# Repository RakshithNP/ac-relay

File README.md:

View this project on [CADLAB.io](https://cadlab.io/project/24087). 

# AC Relay

It is a relay controlled by an ESP8266 and a push button. It is powered by the main AC.

### Firmwares

#### Test

This firmware allows you to test the hardware if needed. It will change the relay status each 400 millisenconds when the button is pressed and it will send the push button status via serial communication.

#### AdafruitIO

This firmware is based in the Adafruit example for comumnicate with its MQTT broker called AdafruitIO. You can see more in <a href="https://io.adafruit.com">io.adafruit.com</a>

In order to use it you should set:

- Your WiFi setting
- You Adafruit user name
- API Key from Adafruit IO
- The MQTT feed which will be used in Adafruit IO

#### MQTT

This firmware allows you to communicate with a MQTT broker. For example, you can install your own MQTT broker in a Raspberry Pi.

This is the actual firmware that I am using at home with this circuit, and it is prepared for being working 24/7. It does:

- Recovery after a power failure.
- Wake up message
- Reconnect message
- Serial debug
- WiFi reconnect if the signal is lost
- MQTT Broker reconnect if the signal is lost

### For future revisions

- `LED`: LED as IO instead of Power LED
- `ESP8266`: ESP8266 as SoC instead of the ESP8266-12E module
- `UPS`: Uninterrupted Power System. Cesar Fernández idea
- `Capacitive button`: A capacitive external button that acts as the push button

***

<br /><span xmlns:dct="http://purl.org/dc/terms/" property="dct:title">Home AC relay</span> by <span xmlns:cc="http://creativecommons.org/ns#" property="cc:attributionName">Enrique Gómez</span> licensed by <a rel="license" href="http://creativecommons.org/licenses/by-sa/4.0/">Creative Commons Attribution-ShareAlike 4.0 International License</a>.<br /><br />

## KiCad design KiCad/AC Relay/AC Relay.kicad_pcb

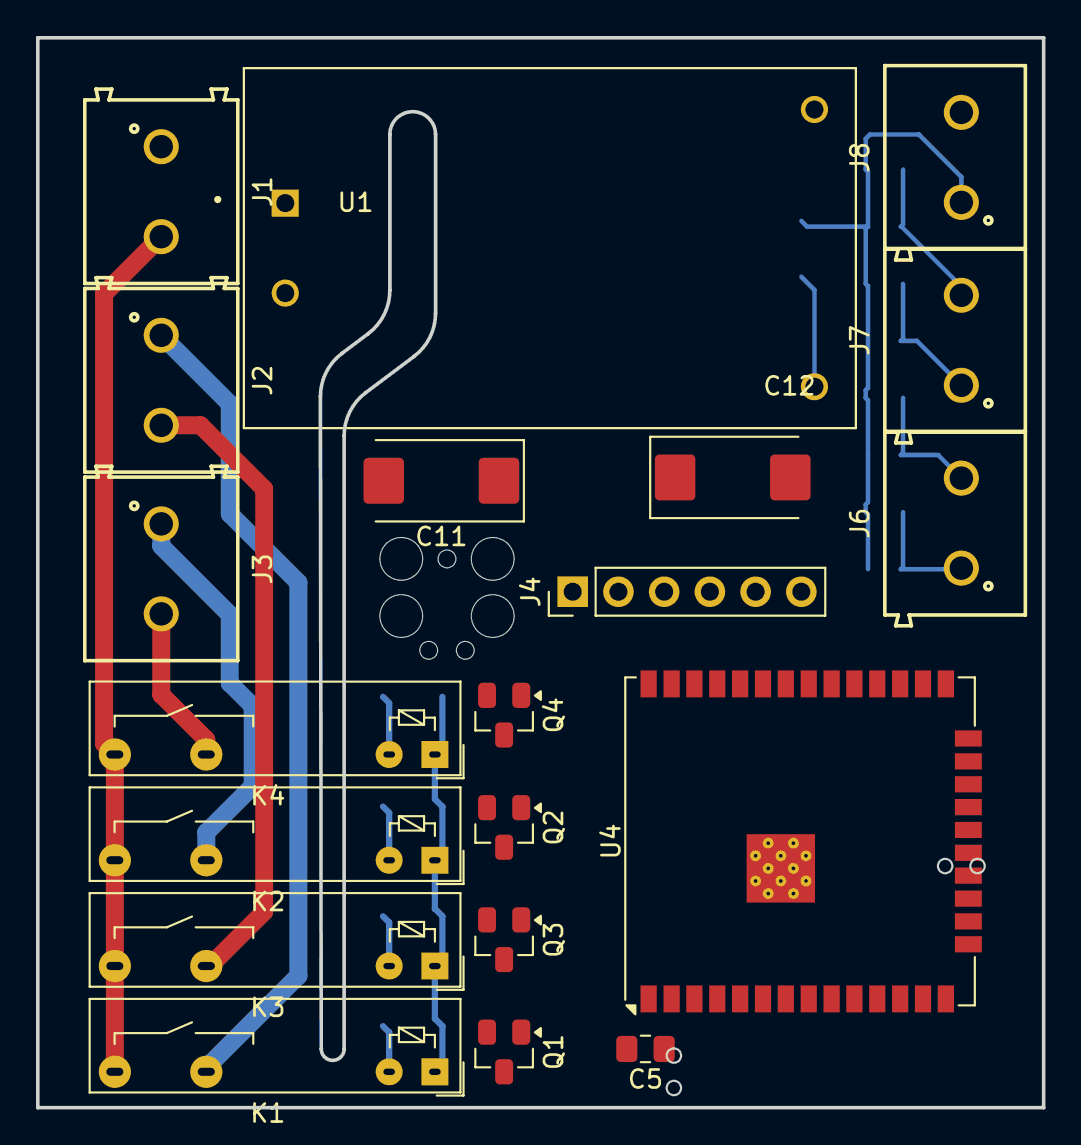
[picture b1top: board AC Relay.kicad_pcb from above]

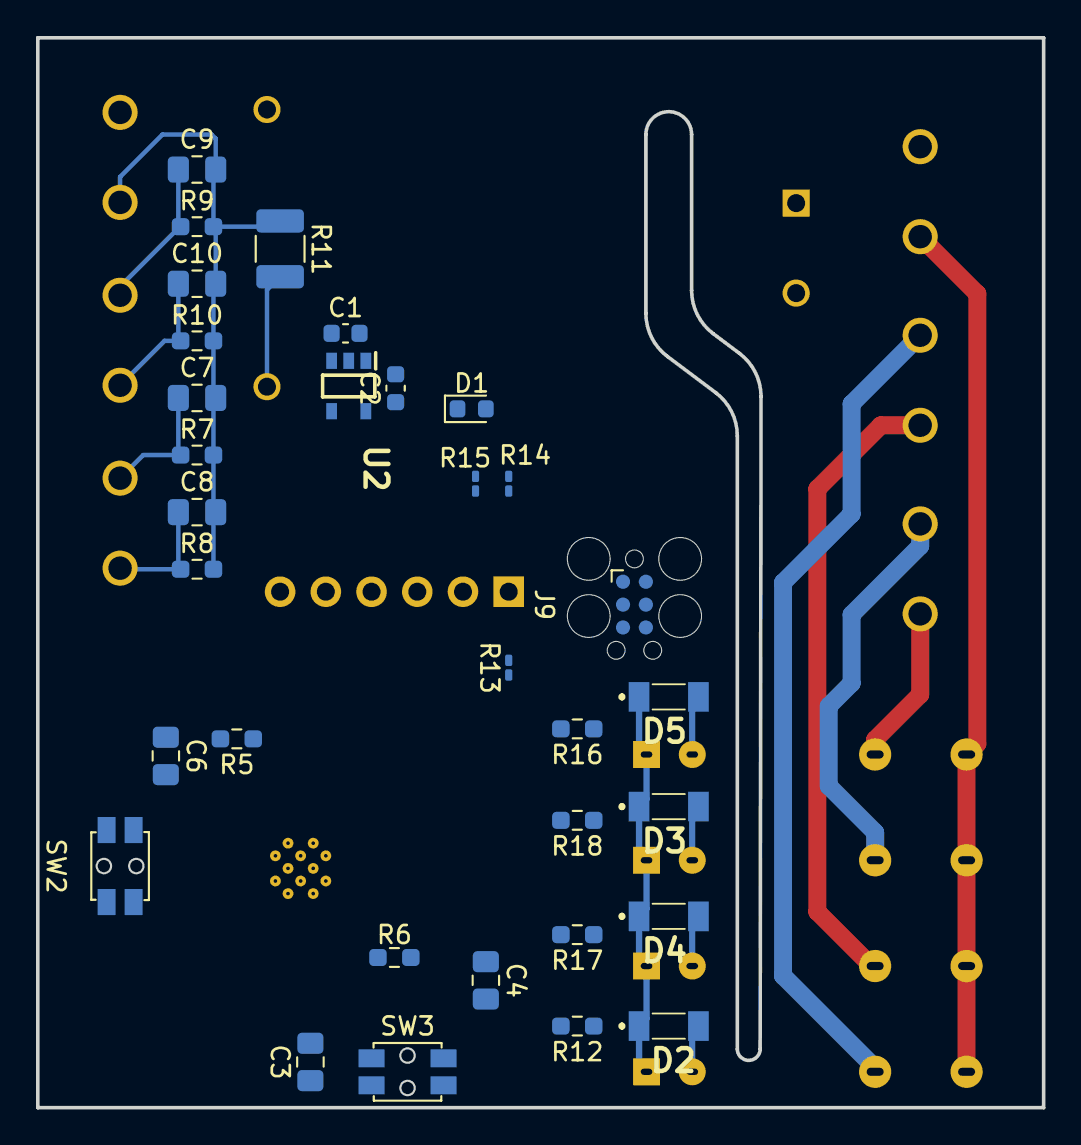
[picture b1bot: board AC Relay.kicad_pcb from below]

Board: 4 copper layers, 55.9 x 59.4 mm, 52 parts (32 on the bottom side), 32 nets.

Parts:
C1, C2: 1uF; C_0603_1608Metric
C3, C5, C6, C7, C8, C9, C10: 0.1uf; C_0805_2012Metric_Pad1.18x1.45mm_HandSolder
C4: 10uf; C_0805_2012Metric_Pad1.18x1.45mm_HandSolder
C11, C12: 100uF T cap; CP_EIA-7343-20_Kemet-V_Pad2.25x2.55mm_HandSolder
D1: LED_verde; LED_0603_1608Metric
D2, D3, D4, D5: LL4148
J1, J2, J3: Screw_Terminal_01x02; 2_terminal_block
J4: Conn_01x06_Female; PinHeader_1x06_P2.54mm_Vertical
J6, J7, J8: TB002-500-02BE; 2_terminal_block_small
J9: Conn_ARM_SWD_TagConnect_TC2030; Tag-Connect_TC2030-IDC-FP_2x03_P1.27mm_Vertical
K1, K2, K3, K4: 1-2071556-1; Relay_SPST_Fanahar_5A
Q1, Q2, Q3, Q4: FDN537N; SuperSOT-3
R5, R7, R8, R9, R10: 10K; R_0603_1608Metric_Pad0.98x0.95mm_HandSolder
R6: 12K; R_0603_1608Metric_Pad0.98x0.95mm_HandSolder
R11: 330R; R_1210_3225Metric_Pad1.30x2.65mm_HandSolder
R12, R16, R17, R18: 1K; R_0603_1608Metric_Pad0.98x0.95mm_HandSolder
R13, R14: 0R; R_0201_0603Metric_Pad0.64x0.40mm_HandSolder
R15: NA; R_0201_0603Metric_Pad0.64x0.40mm_HandSolder
SW2: Boot; SW_SPST_withpost
SW3: Rst; SW_SPST_withpost
U1: HLK-PM01; CONV_HLK-PM01
U2: BU33SD5WG-TR; SOT95P280X125-5N
U4: ESP32-WROOM-32UE

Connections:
+3V3: C2.1, C4.1, C5.1, C12.1, J4.6, R5.1, R6.1, R15.1, U2.5 (VOUT), U4.2 (VDD)
+5V: C1.1, C11.1, D2.1 (K), D3.1 (K), D4.1 (K), D5.1 (K), K1.K1, K2.K1, K3.K1, K4.K1, R11.2, R14.1, U1.4 (+VO), U2.1 (VIN), U2.3 (STBY)
/AC to DC conv/Neutral: J1.1, U1.1 (AC1)
/AC to DC conv/Phase: J1.2, K1.NO, K2.NO, K3.NO, K4.NO, U1.2 (AC2)
/Relay and diver/Rel_sig1: Q1.1 (G), R12.2
/Relay and diver/Rel_sig2: Q3.1 (G), R17.2
/Relay and diver/Rel_sig3: Q2.1 (G), R18.2
/Relay and diver/Rel_sig4: Q4.1 (G), R16.2
/microcontroller/DTR: C6.1, R5.2, R13.1, SW2.1, SW2.2, U4.25 (IO0)
/microcontroller/RX: J4.2, J9.4 (Rx), U4.35 (TXD0/IO1)
/microcontroller/TX: J4.3, J9.2 (Tx), U4.34 (RXD0/IO3)
/microcontroller/Vcc_sel: J4.4, J9.1 (VCC), R14.2, R15.2
GND: C1.2, C2.2, C3.2, C4.2, C5.2, C6.2, C11.2, C12.2, D1.1 (K), J4.5, J9.5 (GND), Q1.3 (S), Q2.3 (S), Q3.3 (S), Q4.3 (S), SW2.3 (K), SW2.4 (A), SW3.1, SW3.2, U1.3 (-VO), U2.2 (GND), U4.1 (GND), U4.15 (GND), U4.38 (GND), U4.39 (GND)
unnamed: C7.1, J6.2, R7.1
unnamed: C8.1, J6.1, R8.1
unnamed: C9.1, J7.2, R9.1
unnamed: C10.1, J7.1, R10.1
unnamed: C7.2, C8.2, C9.2, C10.2, J8.1, R7.2, R8.2, R9.2, R10.2, R11.1
unnamed: D2.2 (A), K1.K2, Q1.2 (D)
unnamed: D3.2 (A), K2.K2, Q2.2 (D)
unnamed: D4.2 (A), K3.K2, Q3.2 (D)
unnamed: D5.2 (A), K4.K2, Q4.2 (D)
unnamed: J2.1, K1.Com
unnamed: J2.2, K3.Com
unnamed: J3.1, K2.Com
unnamed: J3.2, K4.Com
unnamed: J4.1, R13.2
unnamed: C3.1, R6.2, SW3.3 (K), SW3.4 (A), U4.3 (EN)
unnamed: R12.1, U4.26 (IO4)
unnamed: R16.1, U4.29 (IO5)
unnamed: R17.1, U4.27 (IO16)
unnamed: R18.1, U4.28 (IO17)

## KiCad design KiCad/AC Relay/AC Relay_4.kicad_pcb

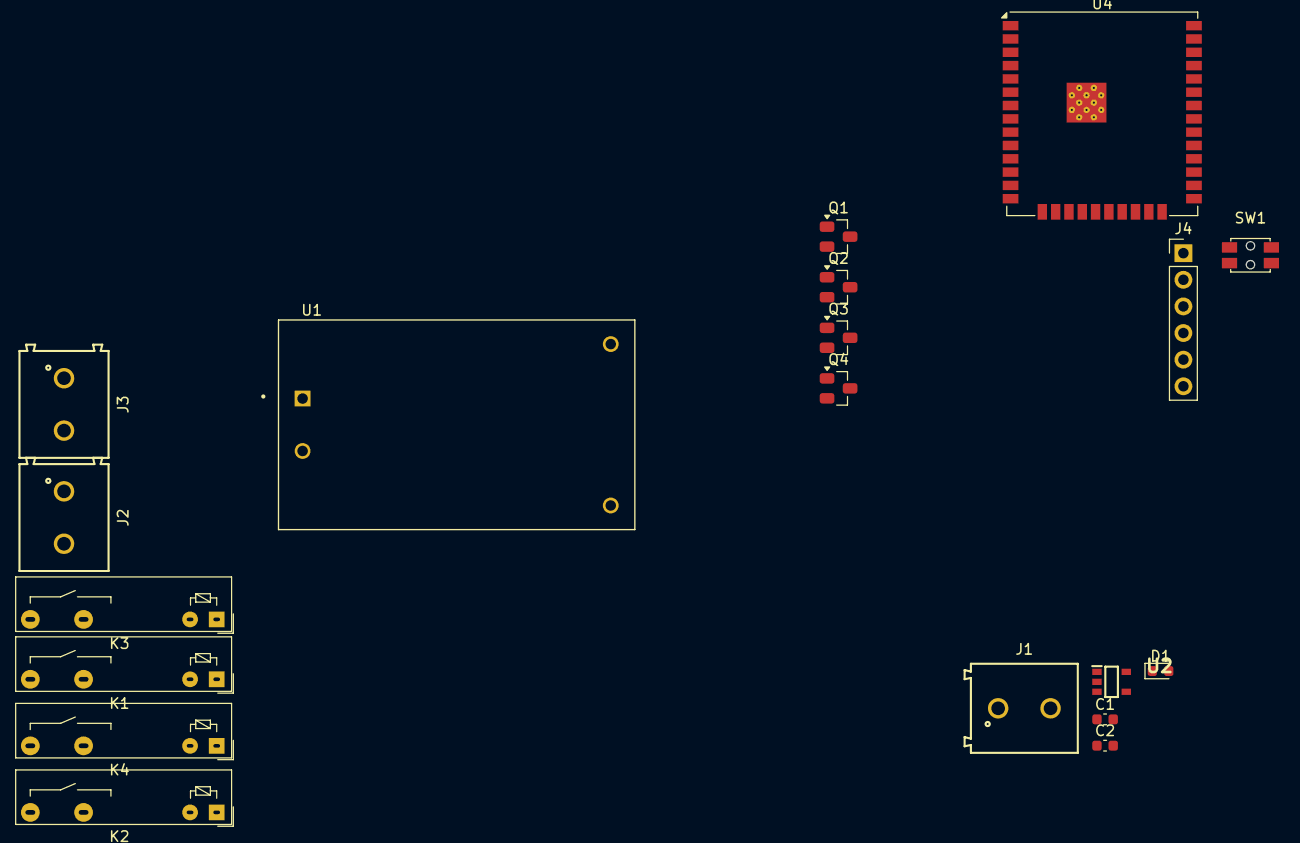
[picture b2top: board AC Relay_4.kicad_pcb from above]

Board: 2 copper layers, 19 parts (0 on the bottom side), 14 nets, no tracks yet.

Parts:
C1, C2: 1uF; C_0603_1608Metric
D1: LED_verde; LED_0603_1608Metric
J1, J2, J3: Screw_Terminal_01x02; 2_terminal_block
J4: Conn_01x06_Female; PinHeader_1x06_P2.54mm_Vertical
K1, K2, K3, K4: 1-2071556-1; Relay_SPST_Fanahar_5A
Q1, Q2, Q3, Q4: FDN537N; SuperSOT-3
SW1: SW_Push; SW_SPST_withpost
U1: HLK-PM01; CONV_HLK-PM01
U2: BU33SD5WG-TR; SOT95P280X125-5N
U4: ESP32-WROOM-32UE

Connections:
+3V3: C2.1, J4.2, U2.5 (VOUT)
+5V: C1.1, K1.K1, K2.K1, K3.K1, K4.K1, U1.4 (+VO), U2.1 (VIN), U2.3 (STBY)
/AC to DC conv/Neutral: J1.2, U1.1 (AC1)
/AC to DC conv/Phase: J1.1, K1.NO, K2.NO, K3.NO, K4.NO, U1.2 (AC2)
GND: C1.2, C2.2, D1.1 (K), J4.1, Q1.3 (S), Q2.3 (S), Q3.3 (S), Q4.3 (S), SW1.3 (K), U1.3 (-VO), U2.2 (GND)
unnamed: K1.K2, Q1.2 (D)
unnamed: K2.K2, Q2.2 (D)
unnamed: K3.K2, Q3.2 (D)
unnamed: K4.K2, Q4.2 (D)
unnamed: J2.1, K1.Com
unnamed: J2.2, K3.Com
unnamed: J3.1, K2.Com
unnamed: J3.2, K4.Com
unnamed: U4.1 (GND), U4.15 (GND), U4.38 (GND), U4.39 (GND)

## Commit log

2021-03-26 kick off
2021-03-26 readme
2021-03-26 license
2021-03-26 Silk screen and bigger solder surface
2021-03-26 update gerbers and docs
2021-03-26 version
2021-03-26 Backlink to CADLAB.io has been added.
2022-09-27 rev: 4 - Change relay to 16 A
2022-10-29 Change diameter of hole
2022-10-29 Change diode footprint
2022-10-29 Update gerbers
2024-05-30 initial commit
    this is the intitial commit
2024-07-22 title edited
2024-07-25 until components placemaent
    done all until com placement, but had isssue in edge cut .
2024-07-25 added cutout
    added cutout at the ac and dc isolatin part
2024-07-25 error elemination
    schametic error elemination
2025-03-27 last update
